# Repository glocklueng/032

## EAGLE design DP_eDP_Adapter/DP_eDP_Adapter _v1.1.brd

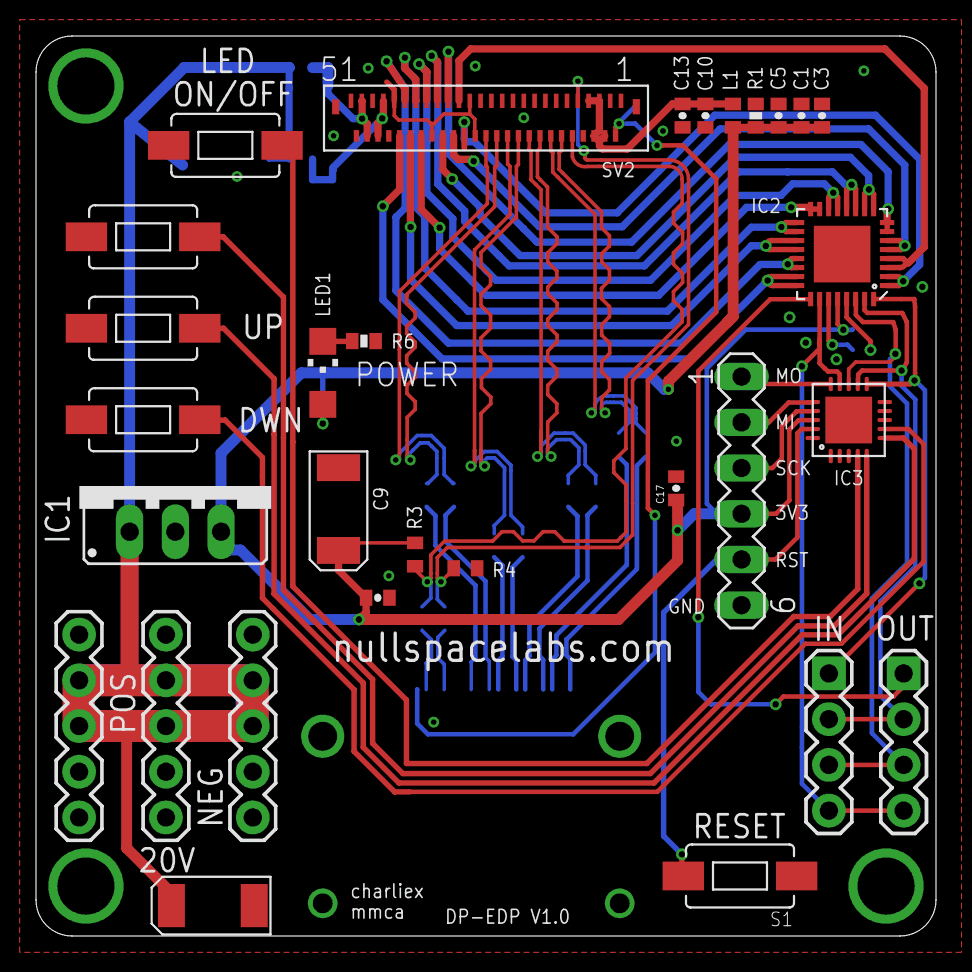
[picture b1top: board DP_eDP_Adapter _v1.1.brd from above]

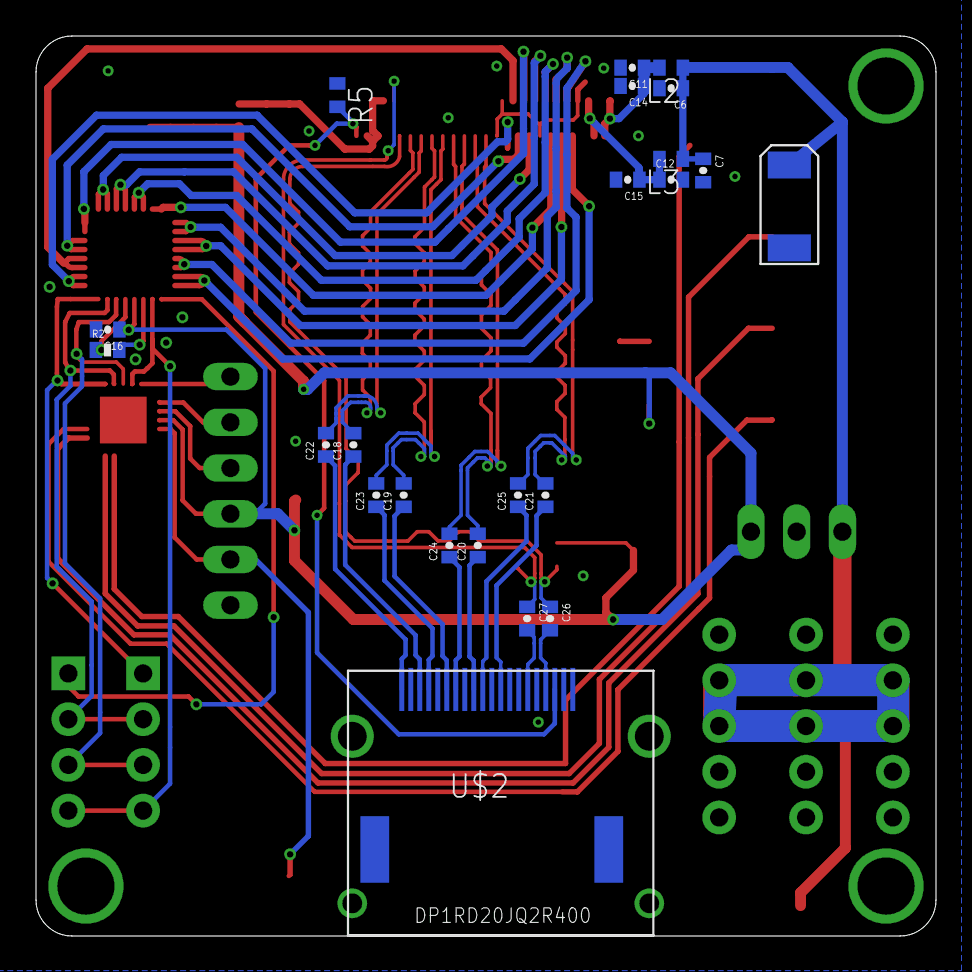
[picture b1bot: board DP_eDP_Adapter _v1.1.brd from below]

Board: 2 copper layers, 50.0 x 50.0 mm, 53 parts (23 on the bottom side), 54 nets.

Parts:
C1, C9: .1uf; 0402-CAP
C2: 10uF 50V; EIA6032
C3, C16, C17: 0.1uF; 0402-CAP
C4: 100uF 50V; EIA6032
C5, C10: 82pF; 0402-CAP
C6, C7, C14, C15: 820pF 50V; 0402-CAP
C8: 10uF; EIA6032
C11, C12: 100pF 50V; 0402-CAP
C13: 1000pF; 0402-CAP
C18, C19, C20, C21, C22, C23, C24, C25, C26, C27: SPARKFUN-PASSIVES_0402-CAP
IC1: 78XXS
IC2: TLC5947XLP; QFN32_XLP
IC3: tiny2313; MLF20
JP1, JP2, JP3: 1X05
L1, L2, L3: 240ohm-300ma; R0402
LED1: LED_CHIPLED_1206
R1, R2, R6: 0402-RES
R3, R4, R5: 100K; R0402
S1, S2, S3, S4, S5: SWITCH-MOMENTARY-2-SMD-1101NE; TACTILE-SWITCH-1101NE
SIG_IN: 1X04
SIG_OUT: 1X04
SV1: MA06-1
SV2: EDP_CONNECTOR; EDP_MOLEX
U$2: DP1RD20JQ2R400; DP_REVERSE_JAE

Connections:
20V: C2.P$1, C4.P$1, C6.1, C7.1, IC1.IN, JP1.2, JP1.3, JP2.2, JP2.3, JP3.2, JP3.3, L2.1, L3.1
+3V3: C1.1, C3.1, C5.1, C8.P$1, C9.1, C16.1, C17.1, IC1.OUT, IC2.28, IC3.P$18, L1.1, LED1.A, R1.2, R3.2, SV1.4
AUX_CH_N: C26.1, R3.1, SV2.P$10
AUX_CH_P: C27.1, R4.2, SV2.P$9
AUX_N: C26.2, U$2.P$17
AUX_P: C27.2, U$2.P$15
BLANK: IC2.30, IC3.P$13, SIG_IN.3, SIG_OUT.3
BUTTON_1: IC3.P$7, S2.P$1
BUTTON_2: IC3.P$6, S3.P$1
BUTTON_3: IC3.P$5, S4.P$1
BUTTON_4: IC3.P$4, S5.P$1
GND: C1.2, C2.P$2, C3.2, C4.P$2, C5.2, C6.2, C7.2, C8.P$2, C9.2, C10.2, C11.2, C12.2, C13.2, C14.2, C15.2, C16.2, C17.2, IC1.GND, IC2.29, IC3.P$8, JP1.4, JP1.5, JP2.4, JP2.5, JP3.4, JP3.5, R1.1, R2.1, R4.1, R5.1, R6.1, S1.P$1, S2.P$2, S3.P$2, S4.P$2, S5.P$2, SV1.6, SV2.P$1, SV2.P$3, SV2.P$8, SV2.P$11, SV2.P$15, SV2.P$19, SV2.P$23, SV2.P$27, SV2.P$28, SV2.P$29, SV2.P$36, SV2.P$43, SV2.P$51, U$2.P$2, U$2.P$5, U$2.P$8, U$2.P$11, U$2.P$16
HPD: R5.2, SV2.P$2, U$2.P$18
LANE0_N: C18.2, SV2.P$12
LANE0_P: C22.2, SV2.P$14
LANE1_N: C19.2, SV2.P$16
LANE1_P: C23.2, SV2.P$18
LANE2_N: C20.2, SV2.P$20
LANE2_P: C24.2, SV2.P$22
LANE3_N: C21.2, SV2.P$24
LANE3_P: C25.2, SV2.P$26
LED_NEG_1A: IC2.23, IC2.24, SV2.P$42
LED_NEG_1B: IC2.11, IC2.12, SV2.P$35
LED_NEG_2A: IC2.21, IC2.22, SV2.P$41
LED_NEG_2B: IC2.9, IC2.10, SV2.P$34
LED_NEG_3A: IC2.19, IC2.20, SV2.P$40
LED_NEG_3B: IC2.7, IC2.8, SV2.P$33
LED_NEG_4A: IC2.17, IC2.18, SV2.P$39
LED_NEG_4B: IC2.5, IC2.6, SV2.P$32
LED_NEG_5A: IC2.15, IC2.16, SV2.P$38
LED_NEG_5B: IC2.3, IC2.4, SV2.P$31
LED_NEG_6A: IC2.13, IC2.14, SV2.P$37
LED_NEG_6B: IC2.1, IC2.2, SV2.P$30
LED_POS_1: C11.1, C14.1, L2.2, SV2.P$48, SV2.P$49
LED_POS_2: C12.1, C15.1, L3.2, SV2.P$45, SV2.P$46
MISO: IC3.P$16, SV1.2
MOSI: IC3.P$15, SV1.1
unnamed: LED1.C, R6.2
unnamed: C18.1, U$2.P$3
unnamed: C22.1, U$2.P$1
unnamed: IC2.27, R2.2
unnamed: C19.1, U$2.P$6
unnamed: C23.1, U$2.P$4
unnamed: C20.1, U$2.P$9
unnamed: C24.1, U$2.P$7
unnamed: C21.1, U$2.P$12
unnamed: C25.1, U$2.P$10
RST: IC3.P$19, S1.P$2, SV1.5
SCK: IC3.P$17, SV1.3
SCLK: IC2.31, IC3.P$12, SIG_IN.2, SIG_OUT.2
SIN: IC2.32, IC3.P$11, SIG_IN.1
SOUT: IC2.25, SIG_OUT.1
VIN: C10.1, C13.1, L1.2, SV2.P$4, SV2.P$5, SV2.P$6, SV2.P$7
XLAT: IC2.26, IC3.P$14, SIG_IN.4, SIG_OUT.4

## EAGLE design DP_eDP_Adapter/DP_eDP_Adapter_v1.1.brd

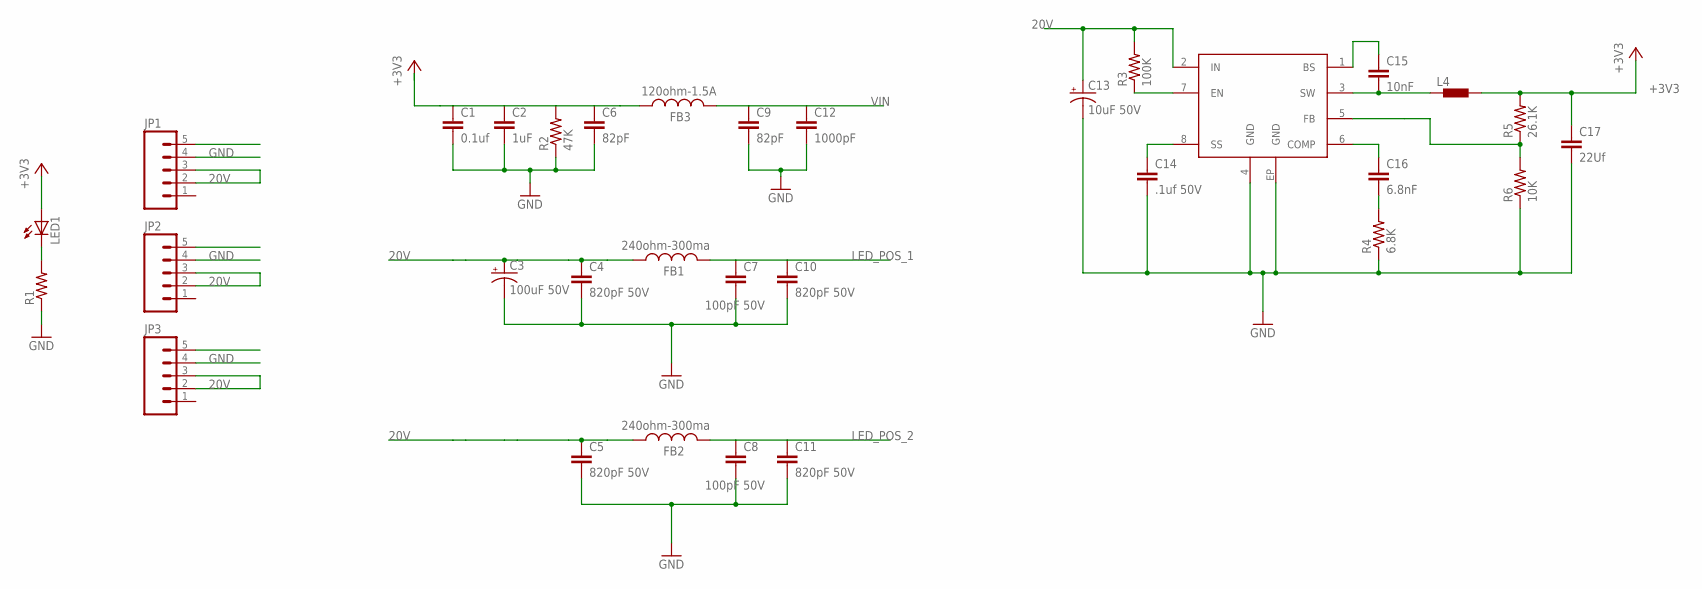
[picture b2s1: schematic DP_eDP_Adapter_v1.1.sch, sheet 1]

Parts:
C1: 0.1uf; 0402-CAP
C2: 1uF; 0402-CAP
C3: 100uF 50V; EIA6032
C4, C5, C10, C11: 820pF 50V; 0402-CAP
C6, C9: 82pF; 0402-CAP
C7, C8: 100pF 50V; 0402-CAP
C12: 1000pF; 0402-CAP
C13: 10uF 50V; EIA6032
C14: .1uf 50V; 0402-CAP
C15: 10nF; 1206
C16: 6.8nF; 0402-CAP
C17: 22Uf; 0402-CAP
FB1, FB2: 240ohm-300ma; R0402
FB3: 120ohm-1.5A; R0402
IC1: AP6502A; SO8-EP
JP1, JP2, JP3: M05PTH; 1X05
L4: INDUCTORS_DR10300520C; 0520C
LED1: LED_LEDCHIPLED_1206; LED_CHIPLED_1206
R1: RESISTOR0402-RES; 0402-RES
R2: 47K; 0402-RES
R3: 100K; 0402-RES
R4: 6.8K; 0402-RES
R5: 26.1K; 0402-RES
R6: 10K; 0402-RES

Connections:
20V: C3.P$1 (+), C4.1, C5.1, C13.P$1 (+), FB1.1, FB2.1, IC1.2 (IN), JP1.2, JP1.3, JP2.2, JP2.3, JP3.2, JP3.3, R3.2
+3V3: C1.1, C2.1, C6.1, C17.1, FB3.1, L4.P$2 (2), LED1.A, R2.2, R5.2; also elsewhere on the board
GND: C1.2, C2.2, C3.P$2 (-), C4.2, C5.2, C6.2, C7.2, C8.2, C9.2, C10.2, C11.2, C12.2, C13.P$2 (-), C14.2, C17.2, IC1.4 (GND), IC1.EP (GND), JP1.4, JP1.5, JP2.4, JP2.5, JP3.4, JP3.5, R1.1, R2.1, R4.1, R6.1; also elsewhere on the board
LED_POS_1: C7.1, C10.1, FB1.2; also elsewhere on the board
LED_POS_2: C8.1, C11.1, FB2.2; also elsewhere on the board
unnamed: IC1.7 (EN), R3.1
unnamed: LED1.C, R1.2
unnamed: C14.1, IC1.8 (SS)
unnamed: C16.1, IC1.6 (COMP)
unnamed: C16.2, R4.2
unnamed: IC1.5 (FB), R5.1, R6.2
unnamed: C15.2, IC1.3 (SW), L4.P$1 (1)
unnamed: C15.1, IC1.1 (BS)
VIN: C9.1, C12.1, FB3.2; also elsewhere on the board

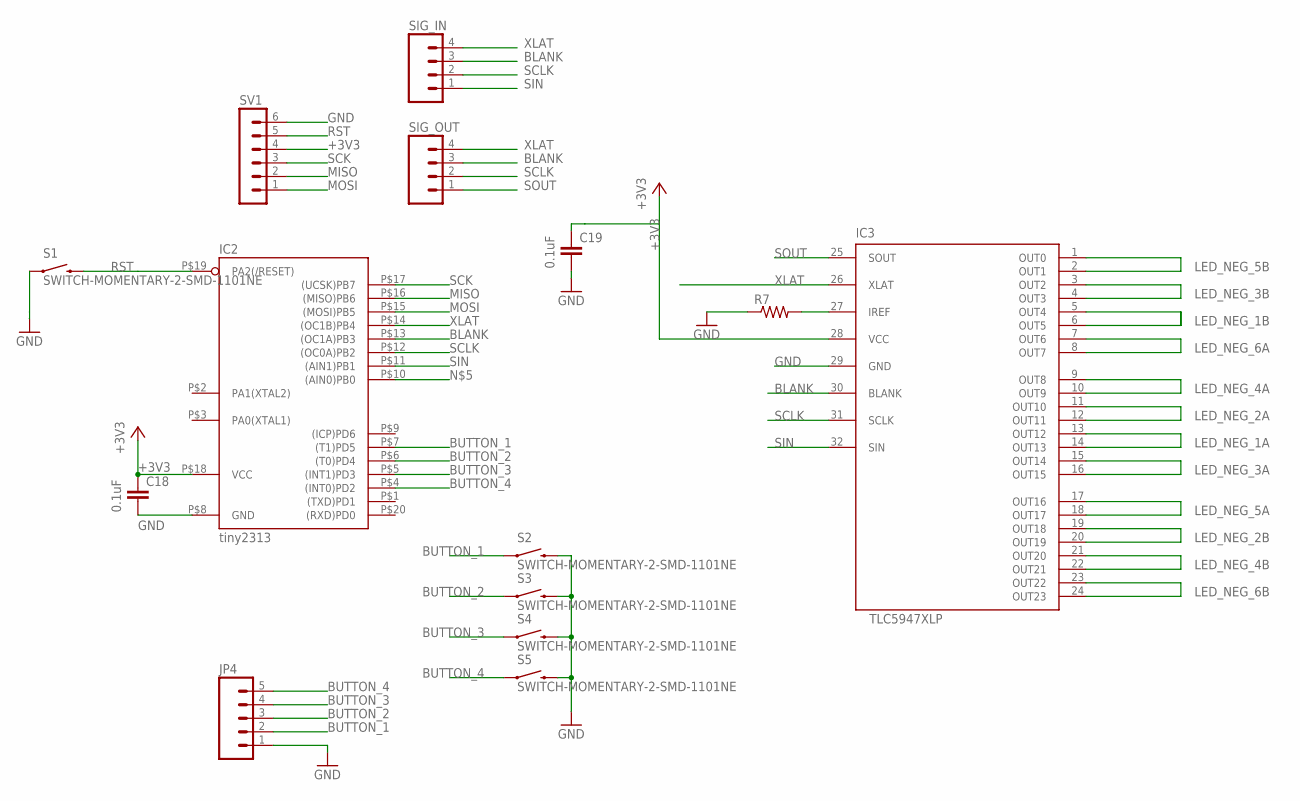
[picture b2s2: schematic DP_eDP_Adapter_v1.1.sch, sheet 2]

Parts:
C18, C19: 0.1uF; 0402-CAP
IC2: tiny2313; MLF20
IC3: TLC5947XLP; QFN32_XLP
JP4: M05PTH; 1X05
R7: RESISTOR0402-RES; 0402-RES
S1, S2, S3, S4, S5: SWITCH-MOMENTARY-2-SMD-1101NE; TACTILE-SWITCH-1101NE
SIG_IN: M04PTH; 1X04
SIG_OUT: M04PTH; 1X04
SV1: MA06-1

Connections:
+3V3: C18.1, C19.1, IC2.P$18 (VCC), IC3.28 (VCC), SV1.4; also elsewhere on the board
BLANK: IC2.P$13 ((OC1A)PB3), IC3.30 (BLANK), SIG_IN.3, SIG_OUT.3
BUTTON_1: IC2.P$7 ((T1)PD5), JP4.2, S2.P$1 (1)
BUTTON_2: IC2.P$6 ((T0)PD4), JP4.3, S3.P$1 (1)
BUTTON_3: IC2.P$5 ((INT1)PD3), JP4.4, S4.P$1 (1)
BUTTON_4: IC2.P$4 ((INT0)PD2), JP4.5, S5.P$1 (1)
GND: C18.2, C19.2, IC2.P$8 (GND), IC3.29 (GND), JP4.1, R7.1, S1.P$1 (1), S2.P$2 (2), S3.P$2 (2), S4.P$2 (2), S5.P$2 (2), SV1.6; also elsewhere on the board
LED_NEG_1A: IC3.13 (OUT12), IC3.14 (OUT13); also elsewhere on the board
LED_NEG_1B: IC3.5 (OUT4), IC3.6 (OUT5); also elsewhere on the board
LED_NEG_2A: IC3.11 (OUT10), IC3.12 (OUT11); also elsewhere on the board
LED_NEG_2B: IC3.19 (OUT18), IC3.20 (OUT19); also elsewhere on the board
LED_NEG_3A: IC3.15 (OUT14), IC3.16 (OUT15); also elsewhere on the board
LED_NEG_3B: IC3.3 (OUT2), IC3.4 (OUT3); also elsewhere on the board
LED_NEG_4A: IC3.9 (OUT8), IC3.10 (OUT9); also elsewhere on the board
LED_NEG_4B: IC3.21 (OUT20), IC3.22 (OUT21); also elsewhere on the board
LED_NEG_5A: IC3.17 (OUT16), IC3.18 (OUT17); also elsewhere on the board
LED_NEG_5B: IC3.1 (OUT0), IC3.2 (OUT1); also elsewhere on the board
LED_NEG_6A: IC3.7 (OUT6), IC3.8 (OUT7); also elsewhere on the board
LED_NEG_6B: IC3.23 (OUT22), IC3.24 (OUT23); also elsewhere on the board
MISO: IC2.P$16 ((MISO)PB6), SV1.2
MOSI: IC2.P$15 ((MOSI)PB5), SV1.1
unnamed: IC3.27 (IREF), R7.2
RST: IC2.P$19 (PA2(/RESET)), S1.P$2 (2), SV1.5
SCK: IC2.P$17 ((UCSK)PB7), SV1.3
SCLK: IC2.P$12 ((OC0A)PB2), IC3.31 (SCLK), SIG_IN.2, SIG_OUT.2
SIN: IC2.P$11 ((AIN1)PB1), IC3.32 (SIN), SIG_IN.1
SOUT: IC3.25 (SOUT), SIG_OUT.1
XLAT: IC2.P$14 ((OC1B)PB4), IC3.26 (XLAT), SIG_IN.4, SIG_OUT.4

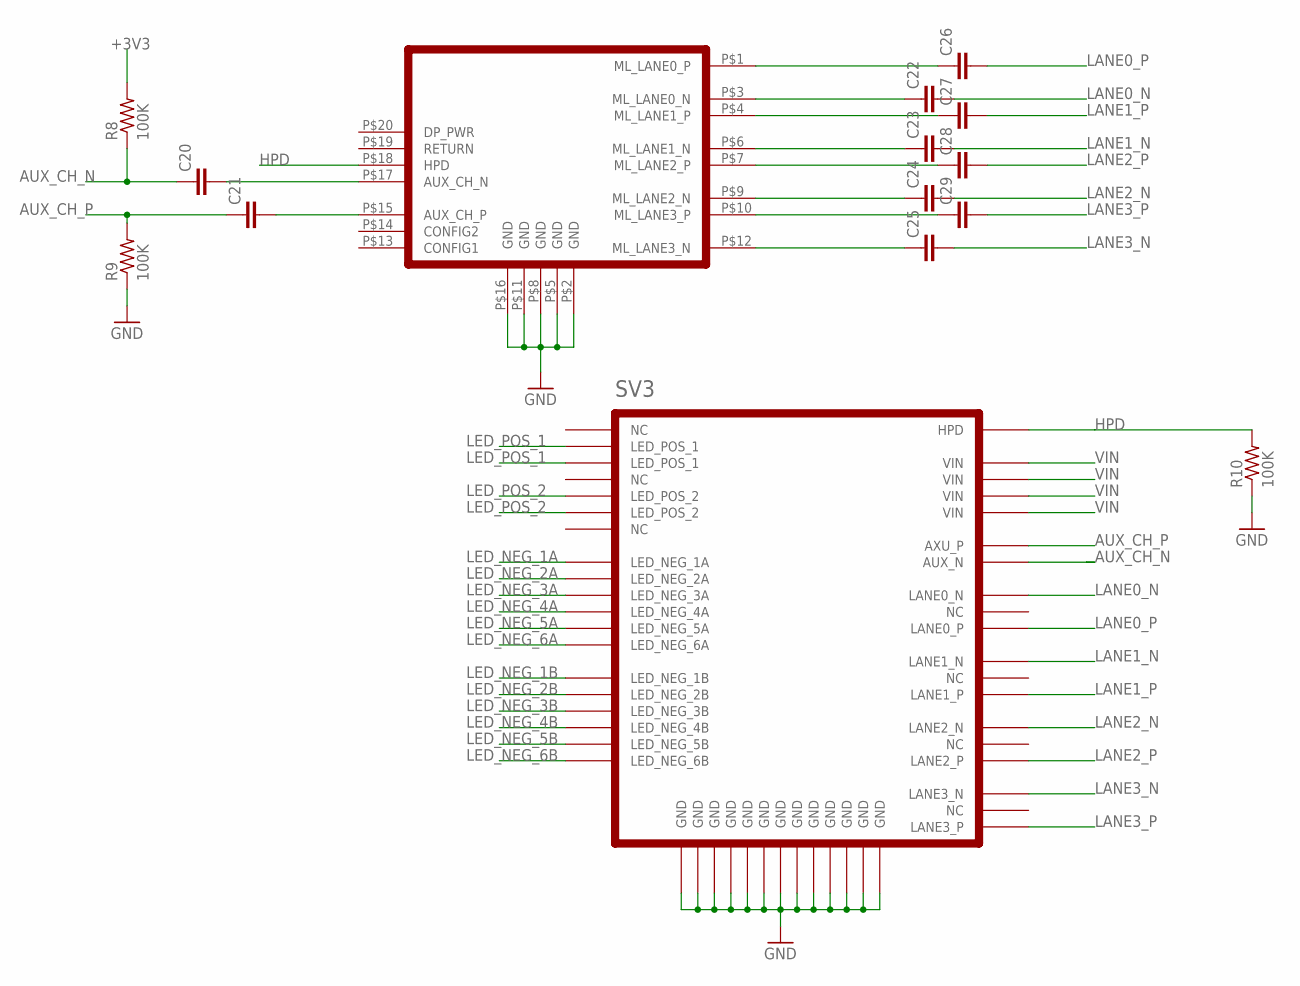
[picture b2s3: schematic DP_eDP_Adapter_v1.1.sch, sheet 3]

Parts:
C20, C21, C22, C23, C24, C25, C26, C27, C28, C29: SPARKFUN-PASSIVES_CAP0402-CAP; SPARKFUN-PASSIVES_0402-CAP
R8, R9, R10: 100K; R0402
SV2: DP1RD20JQ2R400; DP_REVERSE_JAE
SV3: DP_EDP_ADAPTER_EDP_CONNECTOR; DP_EDP_ADAPTER_EDP_MOLEX

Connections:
+3V3: R8.2; also elsewhere on the board
AUX_CH_N: C20.1, R8.1, SV3.P$10 (AUX_N)
AUX_CH_P: C21.1, R9.2, SV3.P$9 (AXU_P)
AUX_N: C20.2, SV2.P$17 (AUX_CH_N)
AUX_P: C21.2, SV2.P$15 (AUX_CH_P)
GND: R9.1, R10.1, SV2.P$2 (GND), SV2.P$5 (GND), SV2.P$8 (GND), SV2.P$11 (GND), SV2.P$16 (GND), SV3.P$1 (GND), SV3.P$3 (GND), SV3.P$8 (GND), SV3.P$11 (GND), SV3.P$15 (GND), SV3.P$19 (GND), SV3.P$23 (GND), SV3.P$27 (GND), SV3.P$28 (GND), SV3.P$29 (GND), SV3.P$36 (GND), SV3.P$43 (GND), SV3.P$51 (GND); also elsewhere on the board
HPD: R10.2, SV2.P$18 (HPD), SV3.P$2 (HPD)
LANE0_N: C22.2, SV3.P$12 (LANE0_N)
LANE0_P: C26.2, SV3.P$14 (LANE0_P)
LANE1_N: C23.2, SV3.P$16 (LANE1_N)
LANE1_P: C27.2, SV3.P$18 (LANE1_P)
LANE2_N: C24.2, SV3.P$20 (LANE2_N)
LANE2_P: C28.2, SV3.P$22 (LANE2_P)
LANE3_N: C25.2, SV3.P$24 (LANE3_N)
LANE3_P: C29.2, SV3.P$26 (LANE3_P)
LED_NEG_1A: SV3.P$42 (LED_NEG_1A); also elsewhere on the board
LED_NEG_1B: SV3.P$35 (LED_NEG_1B); also elsewhere on the board
LED_NEG_2A: SV3.P$41 (LED_NEG_2A); also elsewhere on the board
LED_NEG_2B: SV3.P$34 (LED_NEG_2B); also elsewhere on the board
LED_NEG_3A: SV3.P$40 (LED_NEG_3A); also elsewhere on the board
LED_NEG_3B: SV3.P$33 (LED_NEG_3B); also elsewhere on the board
LED_NEG_4A: SV3.P$39 (LED_NEG_4A); also elsewhere on the board
LED_NEG_4B: SV3.P$32 (LED_NEG_4B); also elsewhere on the board
LED_NEG_5A: SV3.P$38 (LED_NEG_5A); also elsewhere on the board
LED_NEG_5B: SV3.P$31 (LED_NEG_5B); also elsewhere on the board
LED_NEG_6A: SV3.P$37 (LED_NEG_6A); also elsewhere on the board
LED_NEG_6B: SV3.P$30 (LED_NEG_6B); also elsewhere on the board
LED_POS_1: SV3.P$48 (LED_POS_1), SV3.P$49 (LED_POS_1); also elsewhere on the board
LED_POS_2: SV3.P$45 (LED_POS_2), SV3.P$46 (LED_POS_2); also elsewhere on the board
unnamed: C22.1, SV2.P$3 (ML_LANE0_N)
unnamed: C26.1, SV2.P$1 (ML_LANE0_P)
unnamed: C23.1, SV2.P$6 (ML_LANE1_N)
unnamed: C27.1, SV2.P$4 (ML_LANE1_P)
unnamed: C24.1, SV2.P$9 (ML_LANE2_N)
unnamed: C28.1, SV2.P$7 (ML_LANE2_P)
unnamed: C25.1, SV2.P$12 (ML_LANE3_N)
unnamed: C29.1, SV2.P$10 (ML_LANE3_P)
VIN: SV3.P$4 (VIN), SV3.P$5 (VIN), SV3.P$6 (VIN), SV3.P$7 (VIN); also elsewhere on the board

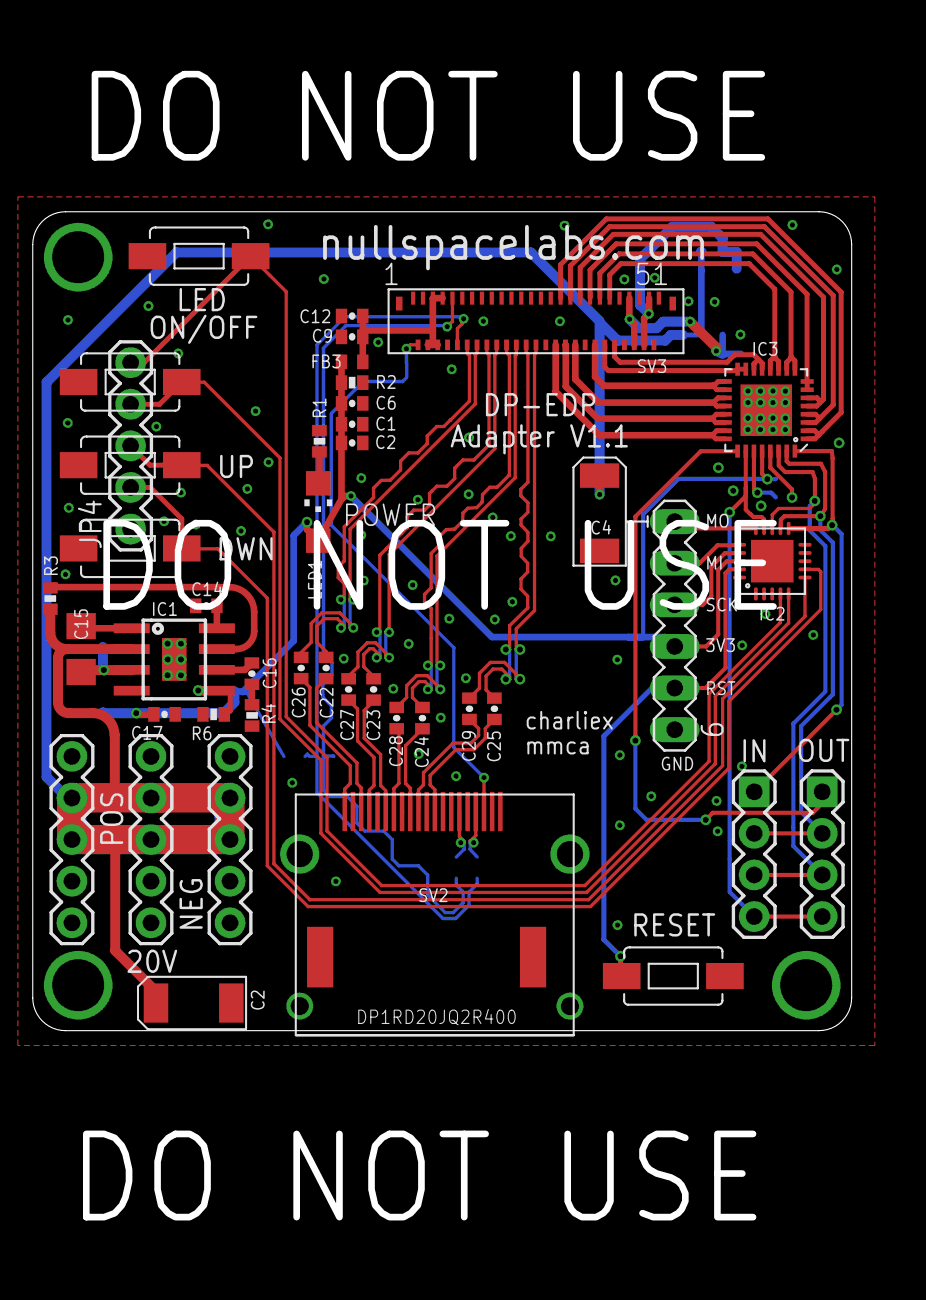
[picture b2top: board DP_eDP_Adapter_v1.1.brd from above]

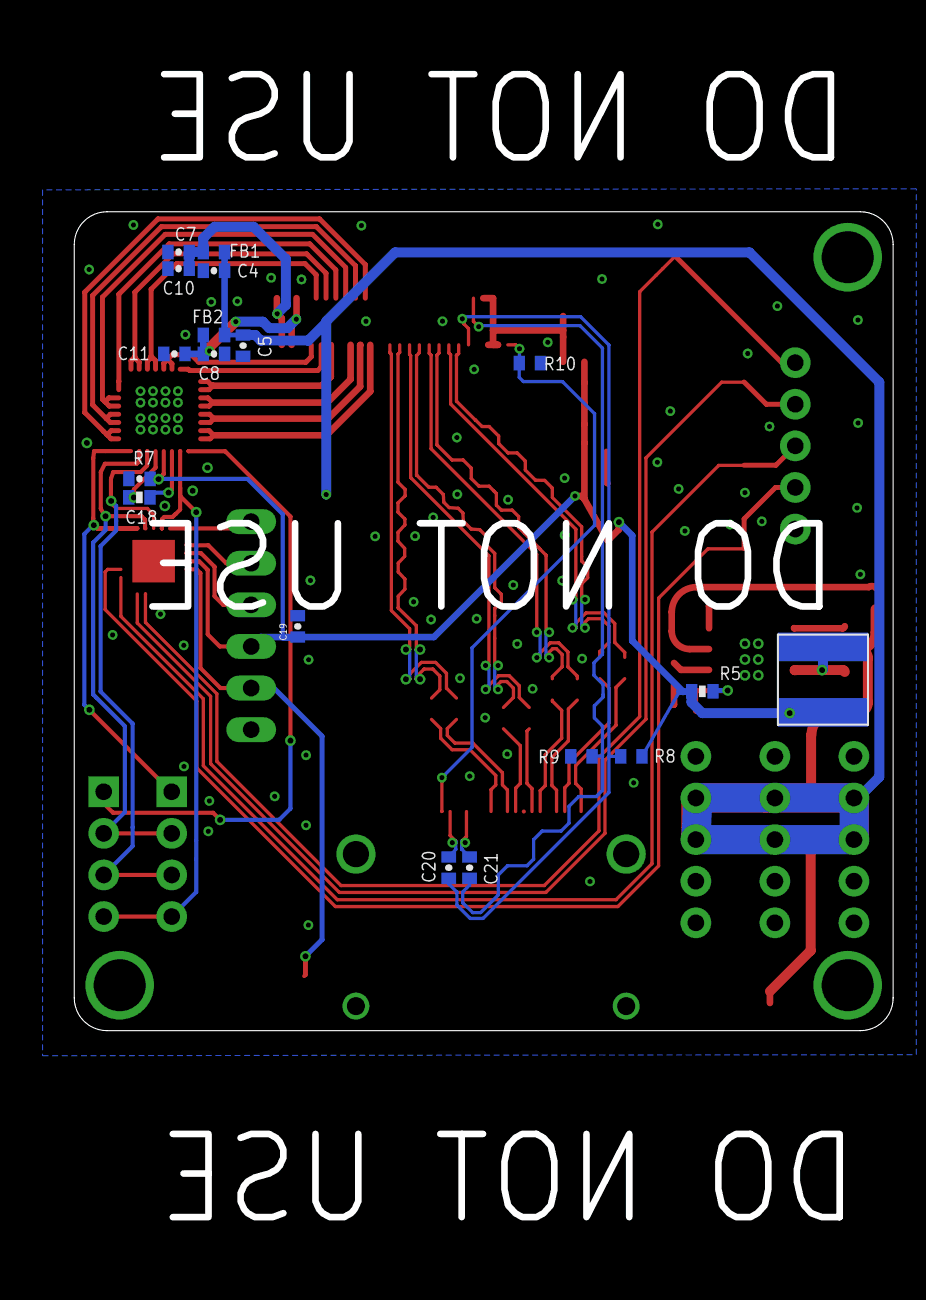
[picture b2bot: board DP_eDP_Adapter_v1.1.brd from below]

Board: 2 copper layers, 50.0 x 50.0 mm, 61 parts (18 on the bottom side), 61 nets.

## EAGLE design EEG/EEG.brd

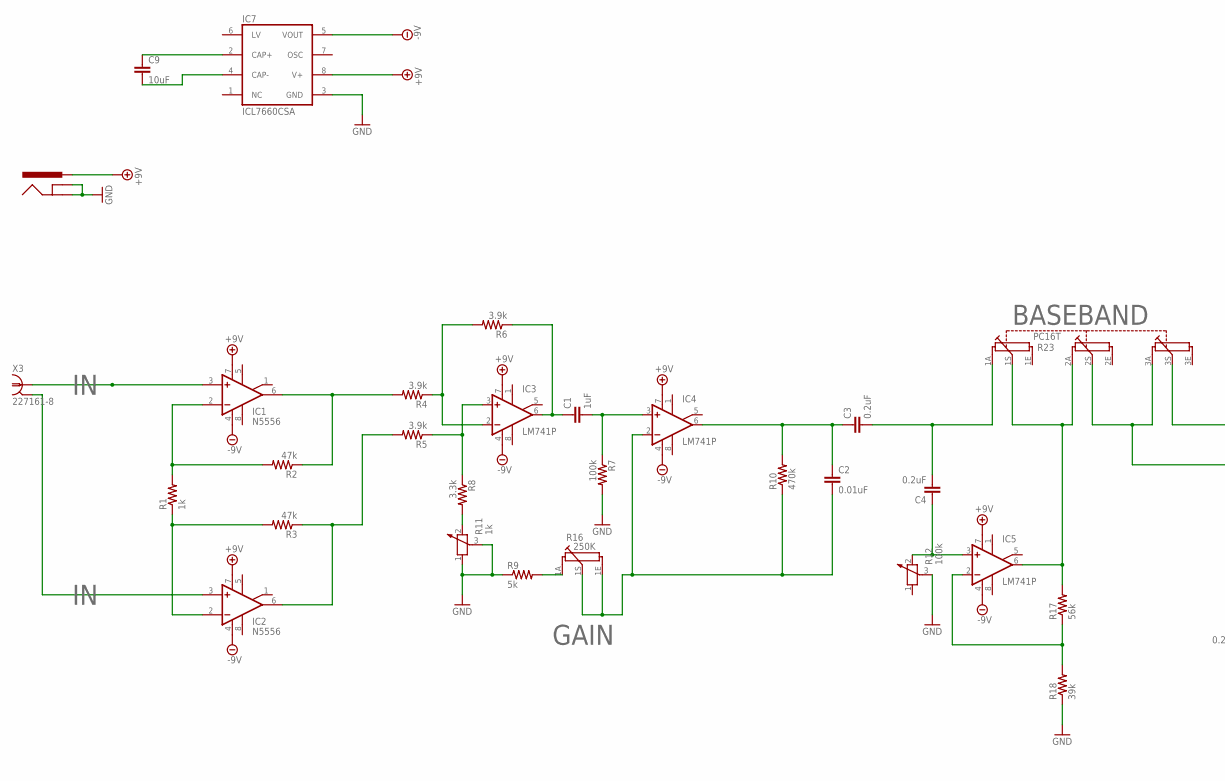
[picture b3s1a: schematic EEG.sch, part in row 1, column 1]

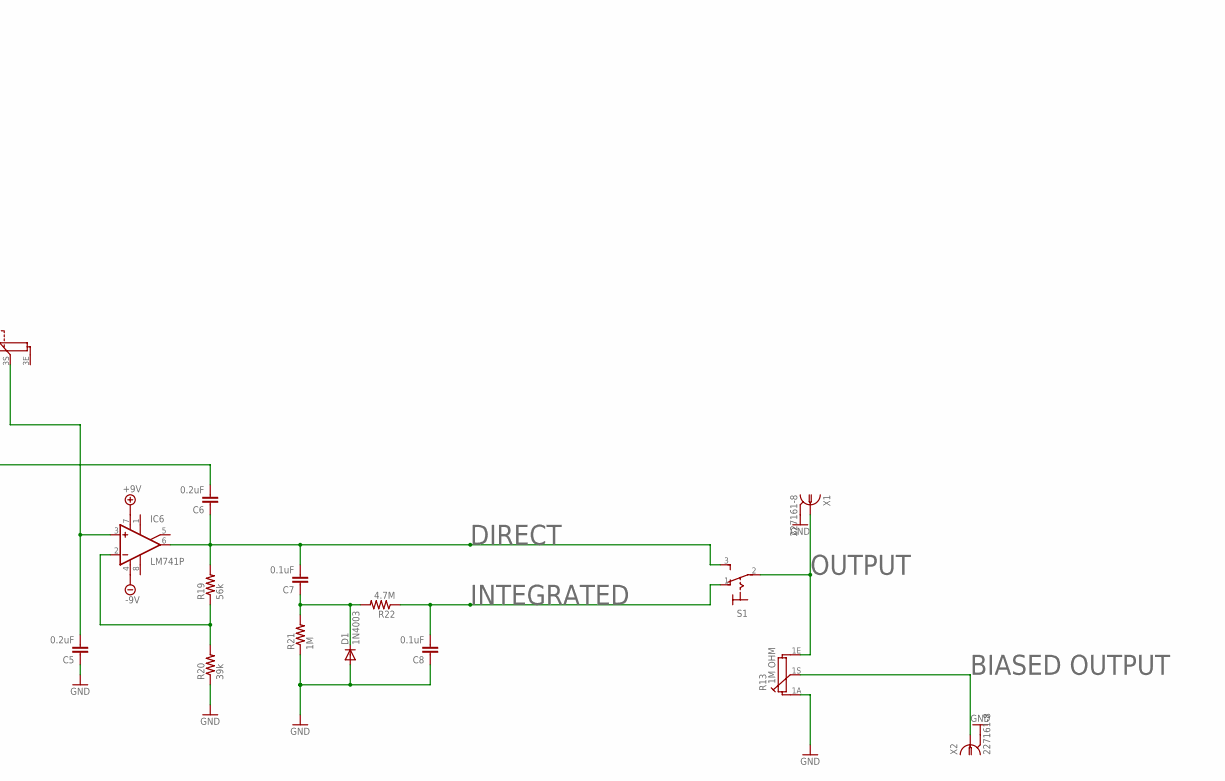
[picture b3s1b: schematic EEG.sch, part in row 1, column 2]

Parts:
C1: 1uF; C1206
C2: 0.01uF; C1206
C3, C4, C5, C6: 0.2uF; C1206
C7, C8: 0.1uF; C1206
C9: 10uF; C1206
D1: 1N4003; DO41-10
IC1, IC2: N5556; DIL08
IC3, IC4, IC5, IC6: LM741P; DIL08
IC7: ICL7660CSA; SO08
J1: SPARKFUN_POWER_JACKPTH; SPARKFUN_POWER_JACK_PTH
R1: 1k; SPARKFUN_1206
R2, R3: 47k; SPARKFUN_1206
R4, R5, R6: 3.9k; SPARKFUN_1206
R7: 100k; SPARKFUN_1206
R8: 3.3k; SPARKFUN_1206
R9: 5k; SPARKFUN_1206
R10: 470k; SPARKFUN_1206
R11: 1k; PT-10
R12: 100k; PT-10
R13: 1M OHM; PC16S
R16: 250K; PC16S
R17, R19: 56k; SPARKFUN_1206
R18, R20: 39k; SPARKFUN_1206
R21: 1M; SPARKFUN_1206
R22: 4.7M; SPARKFUN_1206
R23: PC16T
S1: M9040P
X1, X2, X3: 227161-8; AMP_227161

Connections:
+9V: IC1.7 (V+), IC2.7 (V+), IC3.7 (V+), IC4.7 (V+), IC5.7 (V+), IC6.7 (V+), IC7.8 (V+), J1.PWR
-9V: IC1.4 (V-), IC2.4 (V-), IC3.4 (V-), IC4.4 (V-), IC5.4 (V-), IC6.4 (V-), IC7.5 (VOUT)
BIASOUT: R13.1S, X2.1
DIRECT: C6.1, C7.2, IC6.6 (OUT), R19.2, S1.3 (S)
GND: C5.1, C8.1, D1.A, IC7.3 (GND), J1.GND, J1.GNDBREAK, R7.2, R9.1, R11.1, R11.3, R12.3, R13.1A, R18.1, R20.1, R21.1, X1.2 (GND), X2.2 (GND)
IN0: IC1.3 (+IN), X3.1
IN1: IC2.3 (+IN), X3.2 (GND)
INT: C8.2, R22.1, S1.1 (O)
unnamed: IC1.2 (-IN), R1.2, R2.2
unnamed: IC2.2 (-IN), R1.1, R3.2
unnamed: R9.2, R16.1A
unnamed: IC1.6 (OUT), R2.1, R4.2
unnamed: IC2.6 (OUT), R3.1, R5.2
unnamed: IC3.2 (-IN), R4.1, R6.2
unnamed: IC3.3 (+IN), R5.1, R8.1
unnamed: C1.1, IC3.6 (OUT), R6.1
unnamed: C1.2, IC4.3 (+IN), R7.1
unnamed: R8.2, R11.2
unnamed: C9.1, IC7.2 (CAP+)
unnamed: C2.2, IC4.2 (-IN), R10.1, R16.1E, R16.1S
unnamed: C2.1, C3.1, IC4.6 (OUT), R10.2
unnamed: C3.2, C4.2, R23.1A
unnamed: IC5.6 (OUT), R17.2, R23.1S, R23.2A
unnamed: C7.1, D1.C, R21.2, R22.2
unnamed: C6.2, R23.2S, R23.3A
unnamed: C9.2, IC7.4 (CAP-)
unnamed: C5.2, IC6.3 (+IN), R23.3S
unnamed: C4.1, IC5.3 (+IN), R12.2
unnamed: IC5.2 (-IN), R17.1, R18.2
unnamed: IC6.2 (-IN), R19.1, R20.2
OUT: R13.1E, S1.2, X1.1

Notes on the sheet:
N5556
DIRECT
INTEGRATED
BASEBAND
GAIN
OUTPUT
BIASED OUTPUT

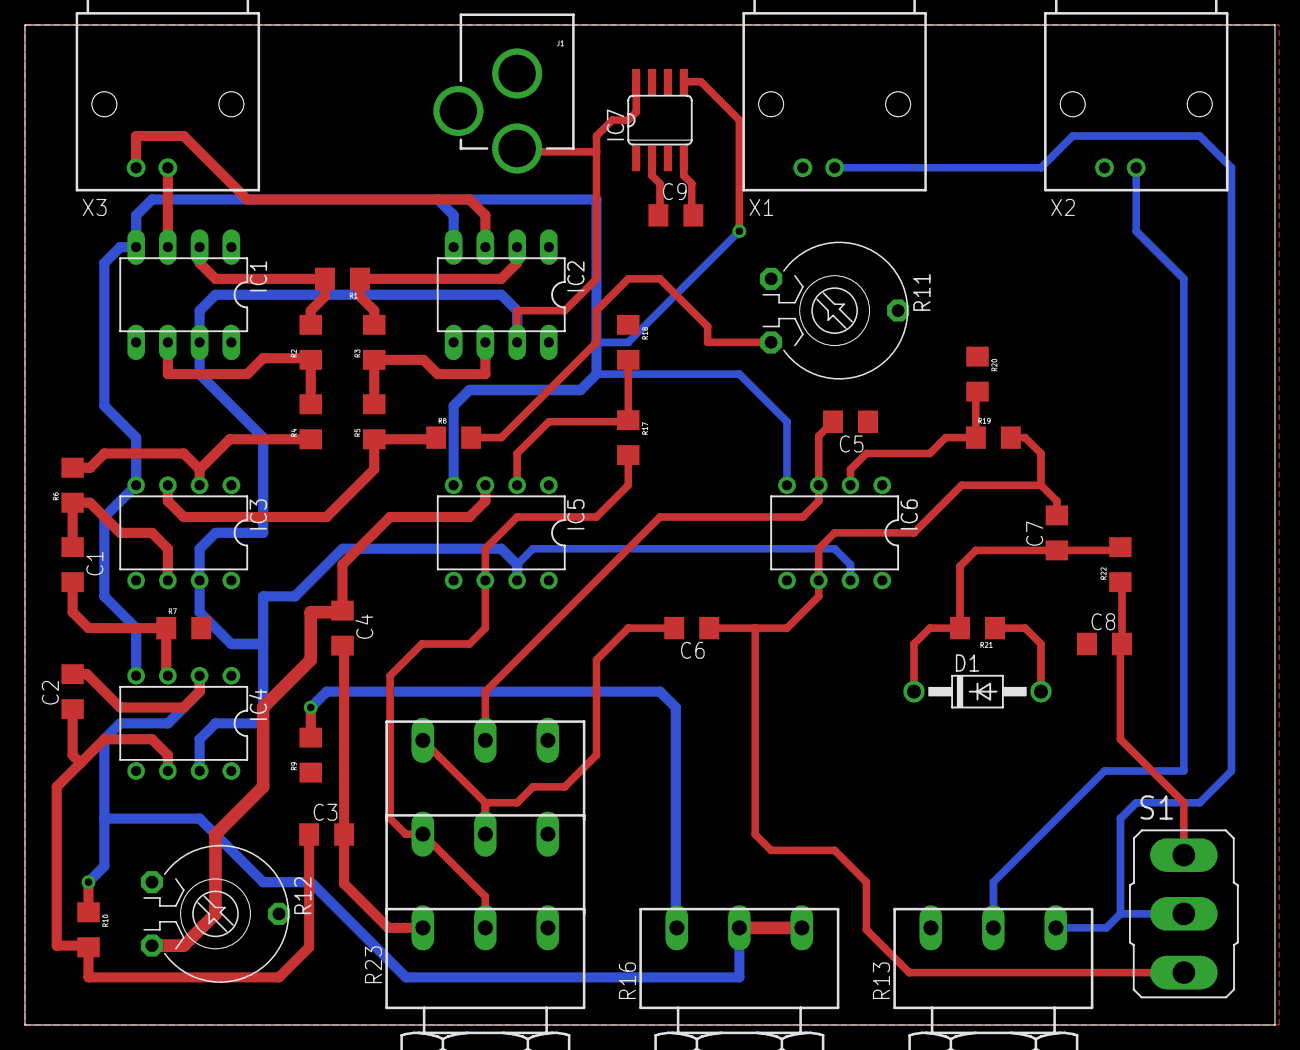
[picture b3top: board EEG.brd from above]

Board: 2 copper layers, 100.0 x 80.0 mm, 43 parts (0 on the bottom side), 31 nets.

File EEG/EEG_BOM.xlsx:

Part | Value | Device | Package | Description | Link
C1 | 1uF | C-EUC1206 | C1206 | CAPACITOR, | http://www.digikey.com/product-detail/en/C3216X7R1E105K085AA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
C2 | 0.01uF | C-EUC1206 | C1206 | CAPACITOR, | http://www.digikey.com/product-detail/en/C3216X7R2J103K115AA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
C3 | 0.2uF | C-EUC1206 | C1206 | CAPACITOR, | http://www.digikey.com/product-detail/en/C3216X7R1E224M/445-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
C4 | 0.2uF | C-EUC1206 | C1206 | CAPACITOR, | http://www.digikey.com/product-detail/en/C3216X7R1E224M/445-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
C5 | 0.2uF | C-EUC1206 | C1206 | CAPACITOR, | http://www.digikey.com/product-detail/en/C3216X7R1E224M/445-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
C6 | 0.2uF | C-EUC1206 | C1206 | CAPACITOR, | http://www.digikey.com/product-detail/en/C3216X7R1E224M/445-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
C7 | 0.1uF | C-EUC1206 | C1206 | CAPACITOR, | http://www.digikey.com/product-detail/en/C3216X7R2A104M160AA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
C8 | 0.1uF | C-EUC1206 | C1206 | CAPACITOR, | http://www.digikey.com/product-detail/en/C3216X7R2A104M160AA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
C9 | 10uF | C-EUC1206 | C1206 | CAPACITOR, | http://www.digikey.com/product-detail/en/C3216Y5V1A106Z%2F0.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
D1 | 1N4003 | 1N4004 | DO41-10 | DIODE | http://www.digikey.com/product-detail/en/1N4003-E3%2F54/1N40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
IC1 | N5556 | MAX430CPA | DIL08 | OP | http://www.digikey.com/product-detail/en/TC7652CPA/TC7652CPA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
IC2 | N5556 | MAX430CPA | DIL08 | OP | http://www.digikey.com/product-detail/en/TC7652CPA/TC7652CPA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
IC3 | LM741P | LM741P | DIL08 | OP | http://www.digikey.com/product-detail/en/LM741CN%2FNOPB/LM74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
IC4 | LM741P | LM741P | DIL08 | OP | http://www.digikey.com/product-detail/en/LM741CN%2FNOPB/LM74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
IC5 | LM741P | LM741P | DIL08 | OP | http://www.digikey.com/product-detail/en/LM741CN%2FNOPB/LM74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
IC6 | LM741P | LM741P | DIL08 | OP | http://www.digikey.com/product-detail/en/LM741CN%2FNOPB/LM74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
IC7 | ICL7660CSA | ICL7660CSA | SO08 | VOLTAGE | http://www.digikey.com/product-detail/en/ICL7660CPA/ICL7660C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
J1 | SPARKFUN_POWER_JACKPTH | SPARKFUN_POWER_JACKPTH | SPARKFUN_POWER_JACK_PTH | Power | http://www.digikey.com/product-detail/en/PJ-002B/CP-002B-ND/96965
R1 | 1k | SPARKFUN_RESISTOR1206 | SPARKFUN_1206 | Resistor | http://www.digikey.com/product-detail/en/ERJ-8GEYJ102V/P1.0K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
R2 | 47k | SPARKFUN_RESISTOR1206 | SPARKFUN_1206 | Resistor | http://www.digikey.com/product-detail/en/ERJ-8GEYJ473V/P47KE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
R3 | 47k | SPARKFUN_RESISTOR1206 | SPARKFUN_1206 | Resistor | http://www.digikey.com/product-detail/en/ERJ-8GEYJ473V/P47KE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
R4 | 3.9k | SPARKFUN_RESISTOR1206 | SPARKFUN_1206 | Resistor | http://www.digikey.com/product-detail/en/ERJ-8GEYJ392V/P3.9K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
R5 | 3.9k | SPARKFUN_RESISTOR1206 | SPARKFUN_1206 | Resistor | http://www.digikey.com/product-detail/en/ERJ-8GEYJ392V/P3.9K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
R6 | 3.9k | SPARKFUN_RESISTOR1206 | SPARKFUN_1206 | Resistor | http://www.digikey.com/product-detail/en/ERJ-8GEYJ392V/P3.9K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
R7 | 100k | SPARKFUN_RESISTOR1206 | SPARKFUN_1206 | Resistor | http://www.digikey.com/product-detail/en/ERJ-8GEYJ104V/P100K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
R8 | 3.3k | SPARKFUN_RESISTOR1206 | SPARKFUN_1206 | Resistor | http://www.digikey.com/product-detail/en/ERJ-8ENF3301V/P3.30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
R9 | 5k | SPARKFUN_RESISTOR1206 | SPARKFUN_1206 | Resistor | http://www.digikey.com/product-detail/en/PNM1206E5001BST5/PN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
R10 | 470k | SPARKFUN_RESISTOR1206 | SPARKFUN_1206 | Resistor | http://www.digikey.com/product-detail/en/ERJ-8GEYJ474V/P470K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
R11 | 1k | POTENTIOMETER_PT-10 | PT-10 | Potentiometer | http://www.digikey.com/product-detail/en/3352E-1-102LF/3352E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
R12 | 100k | POTENTIOMETER_PT-10 | PT-10 | Potentiometer | http://www.digikey.com/product-detail/en/3352E-1-104LF/3352E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
R13 | 1M | OHM | PC16S | PC16S | http://www.digikey.com/product-detail/en/270X232A105B1A1/CT2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
R16 | 250K | PC16S | PC16S | POTENTIOMETER | http://www.digikey.com/product-detail/en/270X232A254B1A1/CT2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
R17 | 56k | SPARKFUN_RESISTOR1206 | SPARKFUN_1206 | Resistor | http://www.digikey.com/product-detail/en/ERJ-8GEYJ563V/P56KE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
R18 | 39k | SPARKFUN_RESISTOR1206 | SPARKFUN_1206 | Resistor | http://www.digikey.com/product-detail/en/ERJ-8GEYJ393V/P39KE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
R19 | 56k | SPARKFUN_RESISTOR1206 | SPARKFUN_1206 | Resistor | http://www.digikey.com/product-detail/en/ERJ-8GEYJ563V/P56KE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
R20 | 39k | SPARKFUN_RESISTOR1206 | SPARKFUN_1206 | Resistor | http://www.digikey.com/product-detail/en/ERJ-8GEYJ393V/P39KE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
R21 | 1M | SPARKFUN_RESISTOR1206 | SPARKFUN_1206 | Resistor | http://www.digikey.com/product-detail/en/ERJ-8GEYJ105V/P1.0M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
R22 | 4.7M | SPARKFUN_RESISTOR1206 | SPARKFUN_1206 | Resistor | http://www.digikey.com/product-detail/en/ERJ-8GEYJ475V/P4.7M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
R23 | PC16T | PC16T | PC16T | POTENTIOMETER | http://www.digikey.com/product-detail/en/270X232A254B1A1/CT2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
R23 | PC16T | PC16T | PC16T | POTENTIOMETER | http://www.digikey.com/product-detail/en/270X232A254B1A1/CT2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
R23 | PC16T | PC16T | PC16T | POTENTIOMETER | http://www.digikey.com/product-detail/en/270X232A254B1A1/CT2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
S1 | M9040P | M9040P | TOGGLE | SWITCH | http://www.digikey.com/product-detail/en/A101SYZQ04/450-1523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
X1 | 227161-8 | 227161-8 | AMP_227161 | JACK, | http://www.digikey.com/product-detail/en/1-1478033-0/A97564-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
X2 | 227161-8 | 227161-8 | AMP_227161 | JACK, | http://www.digikey.com/product-detail/en/1-1478033-0/A97564-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
X3 | 227161-8 | 227161-8 | AMP_227161 | JACK, | http://www.digikey.com/product-detail/en/1-1478033-0/A97564-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

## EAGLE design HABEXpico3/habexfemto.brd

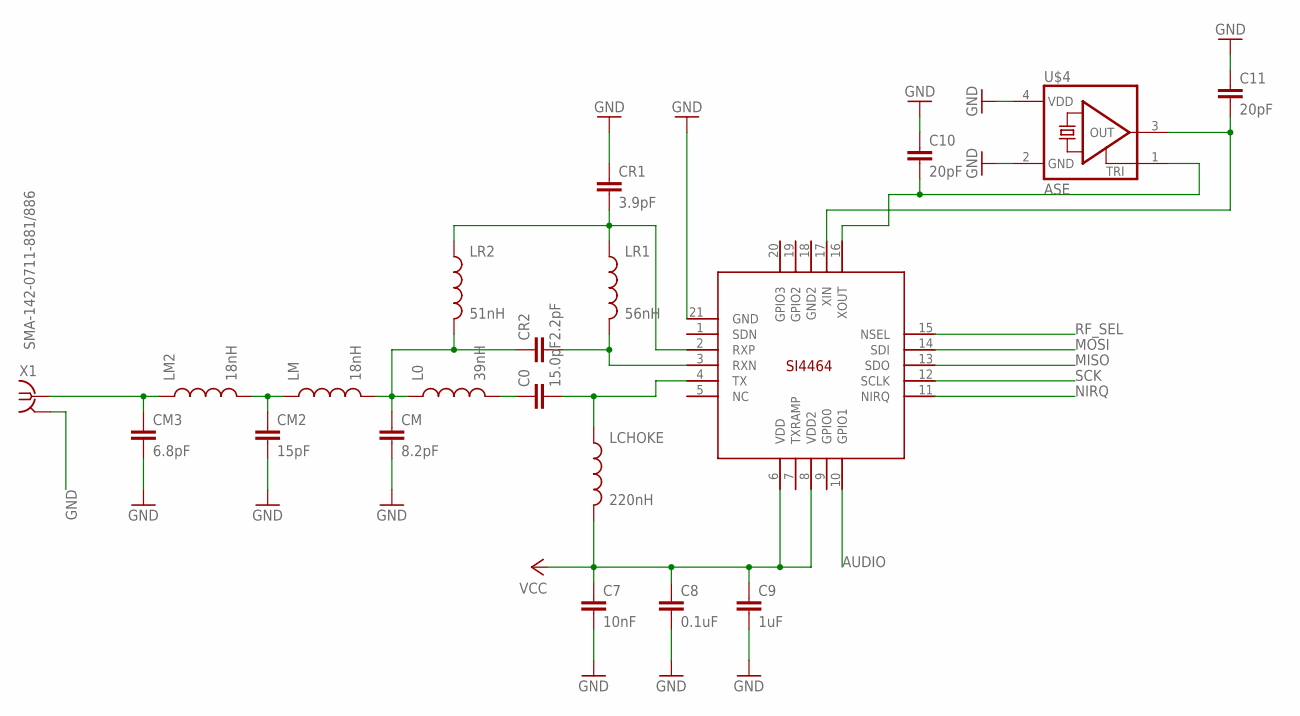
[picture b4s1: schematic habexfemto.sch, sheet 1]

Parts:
C0: 15.0pF; 0402-CAP
C7: 10nF; 0402-CAP
C8: 0.1uF; 0402-CAP
C9: 1uF; 0402-CAP
C10, C11: 20pF; 0402-CAP
CM: 8.2pF; 0402-CAP
CM2: 15pF; 0402-CAP
CM3: 6.8pF; 0402-CAP
CR1: 3.9pF; 0402-CAP
CR2: 2.2pF; 0402-CAP
L0: 39nH; C0402
LCHOKE: 220nH; C0402
LM, LM2: 18nH; C0402
LR1: 56nH; C0402
LR2: 51nH; C0402
U$1: SI4464; QFN20+GNDPAD
U$4: ASE
X1: SMA-142-0711-881/886; J502-ND-142-0711-881/886

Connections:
AUDIO: U$1.10 (GPIO1); also elsewhere on the board
CR2: CM.1, CR2.1, L0.1, LM.2, LR2.2
GND: C7.2, C8.2, C9.2, C10.1, C11.1, CM.2, CM2.2, CM3.2, CR1.1, U$1.21 (GND), U$4.2 (GND), U$4.4 (VDD), X1.G@1 (2), X1.G@2 (2), X1.G@3 (2), X1.G@4 (2); also elsewhere on the board
MISO: U$1.13 (SDO); also elsewhere on the board
MOSI: U$1.14 (SDI); also elsewhere on the board
unnamed: C0.2, LCHOKE.1, U$1.4 (TX)
unnamed: CR2.2, LR1.2, U$1.3 (RXN)
unnamed: CR1.2, LR1.1, LR2.1, U$1.2 (RXP)
unnamed: C0.1, L0.2
unnamed: C11.2, U$1.17 (XIN), U$4.3 (OUT)
unnamed: CM2.1, LM.1, LM2.2
unnamed: CM3.1, LM2.1, X1.1
unnamed: C10.2, U$1.16 (XOUT), U$4.1 (TRI)
NIRQ: U$1.11 (NIRQ); also elsewhere on the board
RF_SEL: U$1.15 (NSEL); also elsewhere on the board
SCK: U$1.12 (SCLK); also elsewhere on the board
VCC: C7.1, C8.1, C9.1, LCHOKE.2, U$1.6 (VDD), U$1.8 (VDD2); also elsewhere on the board

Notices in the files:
parts and their libraries:
SparkFun-Passives: Licensing: CC v3.0 Share-Alike You are welcome to use this library for commercial purposes.
